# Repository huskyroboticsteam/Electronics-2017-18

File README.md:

# Electronics-2017-18

This is the 2017-18 Husky Robotics repository for electronics board designs and everything else electronics!

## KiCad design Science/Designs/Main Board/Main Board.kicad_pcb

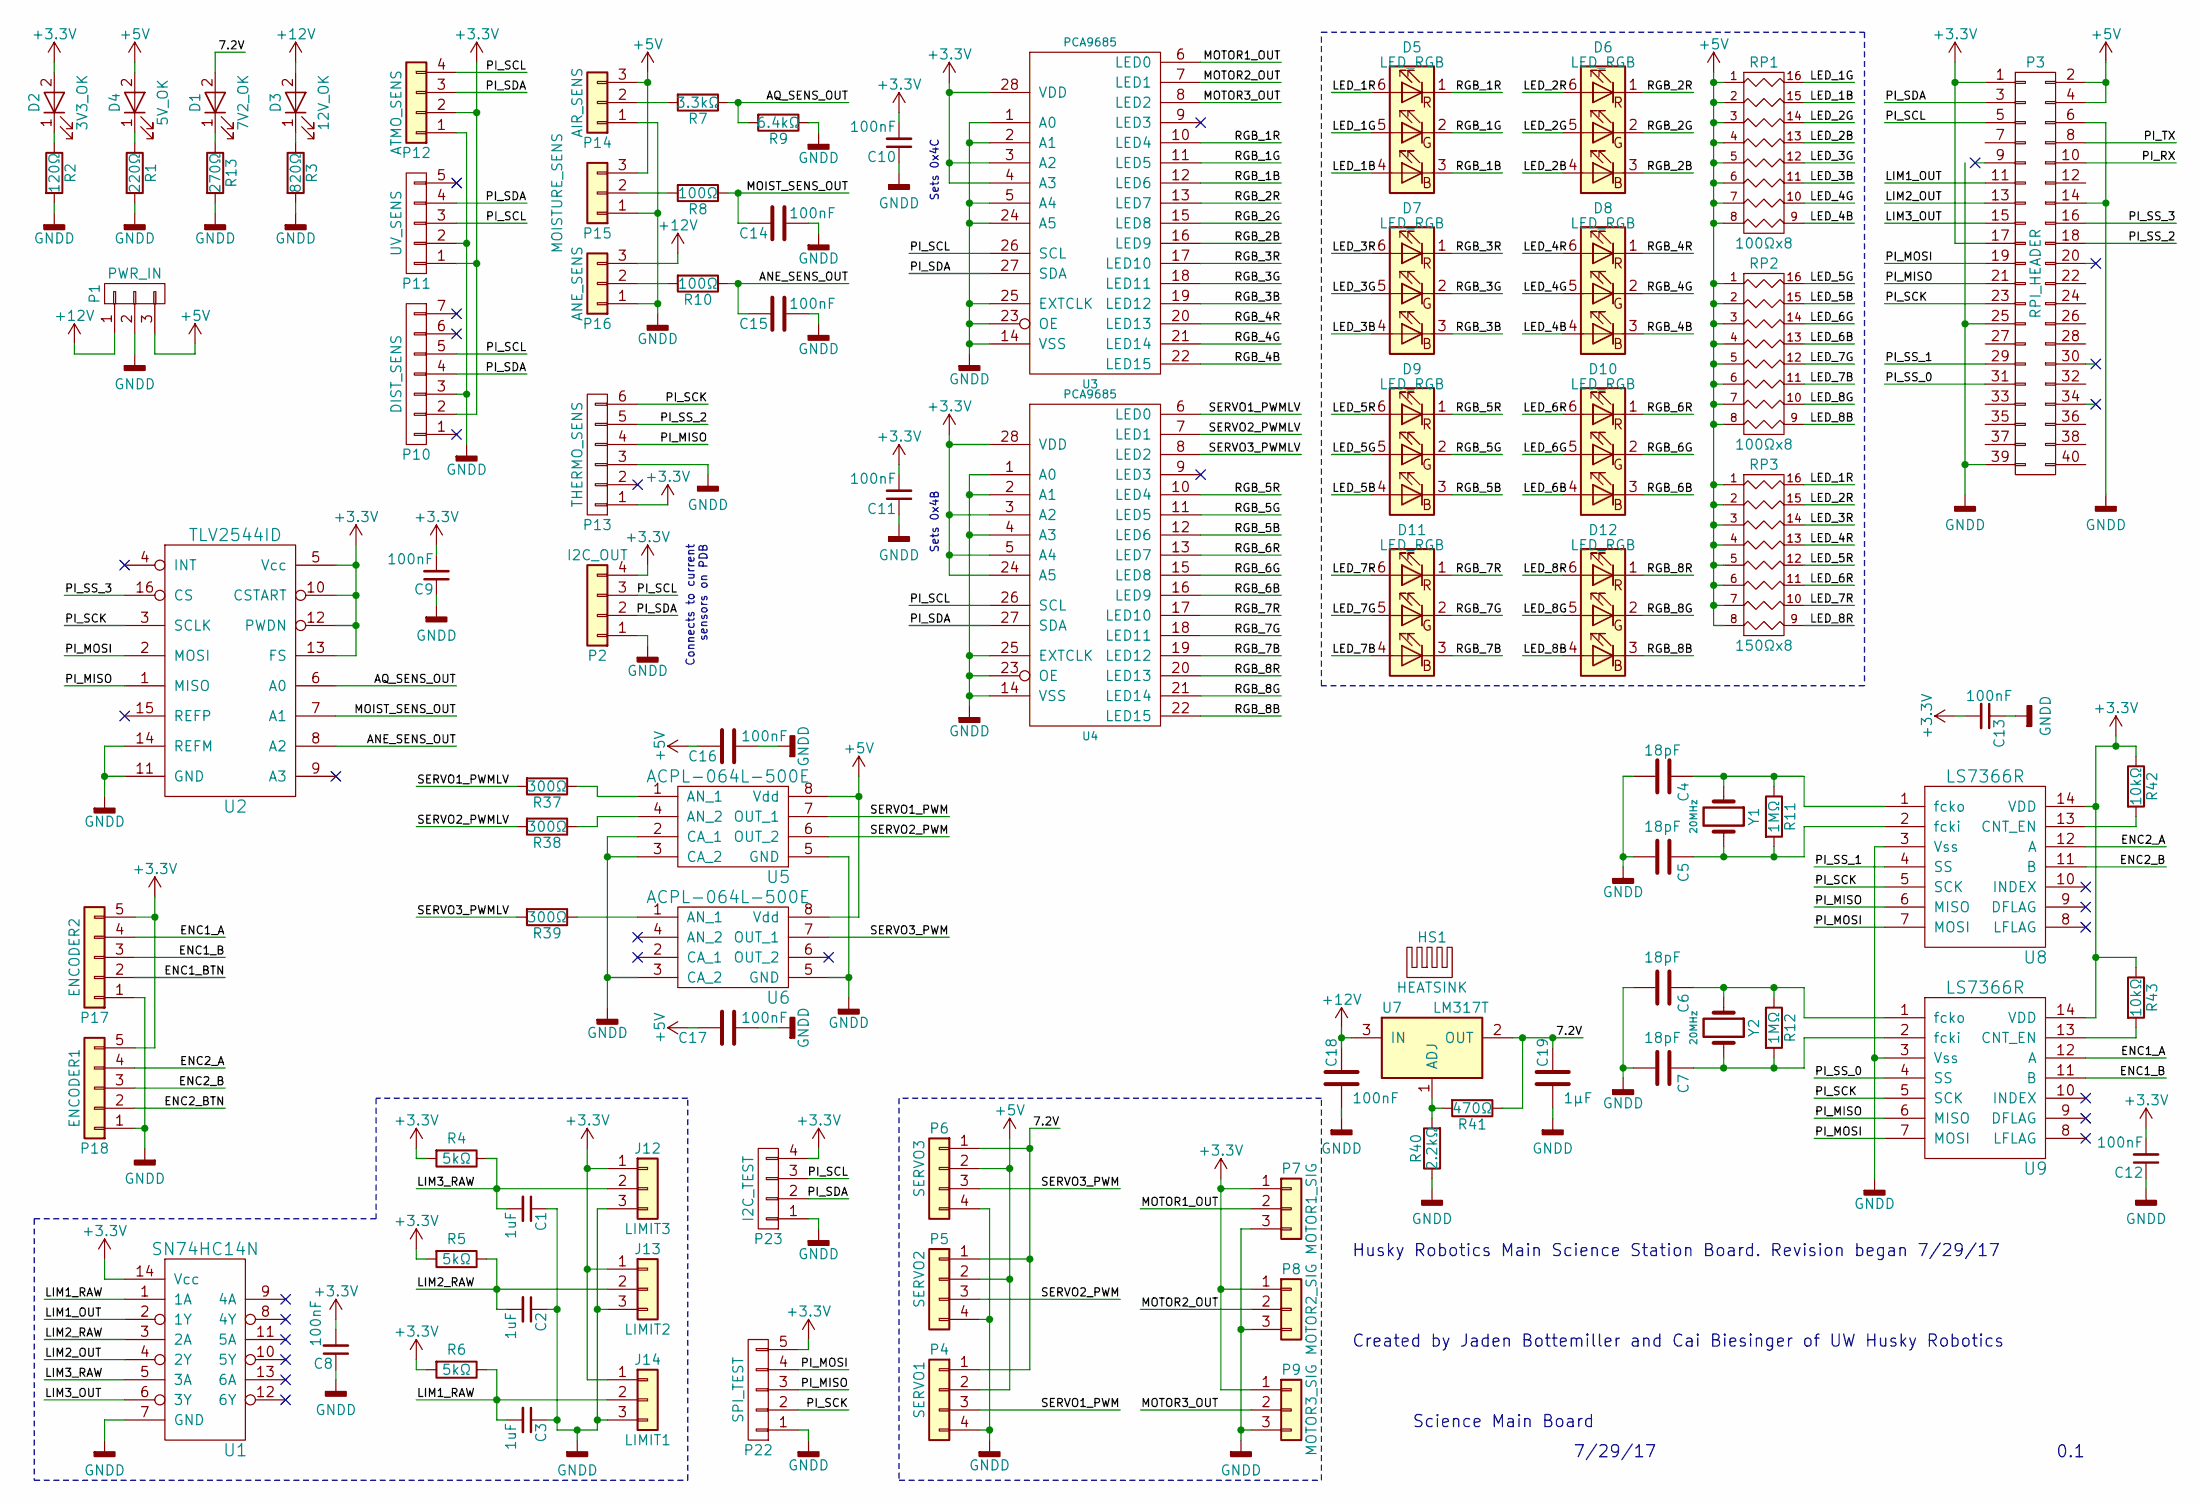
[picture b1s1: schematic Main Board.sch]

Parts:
C1, C2, C3: 1uF; C_1206_HandSoldering
C4, C5, C6, C7: 18pF; C_1206_HandSoldering
C8, C9, C10, C11, C12, C13, C14, C15, C16, C17, C18: 100nF; C_1206_HandSoldering
C19: 1µF; C_1206_HandSoldering
D1: 7V2_OK; LED_D5.0mm
D2: 3V3_OK; LED_D5.0mm
D3: 12V_OK; LED_D5.0mm
D4: 5V_OK; LED_D5.0mm
D5, D6, D7, D8, D9, D10, D11, D12: LED_RGB; SLV6A-FKB
HS1: HEATSINK; AAVID_531202B02500G
J12: LIMIT3; MOLEX_22-23-2031
J13: LIMIT2; MOLEX_22-23-2031
J14: LIMIT1; MOLEX_22-23-2031
P1: PWR_IN; PHOENIX_1792232
P2: I2C_OUT; MOLEX_22-23-2041
P3: RPI_HEADER; RPi-3B
P4: SERVO1; MOLEX_22-23-2041
P5: SERVO2; MOLEX_22-23-2041
P6: SERVO3; MOLEX_22-23-2041
P7: MOTOR1_SIG; MOLEX_22-23-2031
P8: MOTOR2_SIG; MOLEX_22-23-2031
P9: MOTOR3_SIG; MOLEX_22-23-2031
P10: DIST_SENS; MOLEX_22-23-2071
P11: UV_SENS; MOLEX_22-23-2051
P12: ATMO_SENS; MOLEX_22-23-2041
P13: THERMO_SENS; MOLEX_22-23-2061
P14: AIR_SENS; MOLEX_22-23-2031
P15: MOISTURE_SENS; MOLEX_22-23-2031
P16: ANE_SENS; MOLEX_22-23-2031
P17: ENCODER2; MOLEX_22-23-2051
P18: ENCODER1; MOLEX_22-23-2051
P22: SPI_TEST; Pin_Header_Straight_1x05_Pitch2.54mm
P23: I2C_TEST; Pin_Header_Straight_1x04_Pitch2.54mm
R1: 220Ω; R_1206_HandSoldering
R2: 120Ω; R_1206_HandSoldering
R3: 820Ω; R_1206_HandSoldering
R4, R5, R6: 5kΩ; R_1206_HandSoldering
R7: 3.3kΩ; R_1206_HandSoldering
R8, R10: 100Ω; R_1206_HandSoldering
R9: 6.4kΩ; R_1206_HandSoldering
R11, R12: 1MΩ; R_1206_HandSoldering
R13: 270Ω; R_1206_HandSoldering
R37, R38, R39: 300Ω; R_1206_HandSoldering
R40: 2.2kΩ; R_1206_HandSoldering
R41: 470Ω; R_1206_HandSoldering
R42, R43: 10kΩ; R_1206_HandSoldering
RP1, RP2: 100Ωx8; SOIC-16_3.9x9.9mm_Pitch1.27mm
RP3: 150Ωx8; SOIC-16_3.9x9.9mm_Pitch1.27mm
U1: SN74HC14N; SOIC-14_3.9x8.7mm_Pitch1.27mm
U2: TLV2544ID; SOIC-16_3.9x9.9mm_Pitch1.27mm
U3, U4: PCA9685; TSSOP-28_4.4x9.7mm_Pitch0.65mm
U5, U6: ACPL-064L-500E; SOIC-8_3.9x4.9mm_Pitch1.27mm
U7: LM317T; TO-220-3_Vertical
U8, U9: LS7366R; SOIC-14_3.9x8.7mm_Pitch1.27mm
Y1, Y2: 20MHz; HC-49USX

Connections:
+3V3: C8.2, C9.2, C10.2, C11.2, C12.2, C13.2, D2.2 (A), J12.1, J13.1, J14.1, P2.4, P3.1, P3.17, P7.1, P8.1, P9.1, P10.2, P11.1, P12.2, P13.1, P17.5, P18.5, P22.5, P23.4, R4.2, R5.2, R6.2, R42.1, R43.1, U1.14 (Vcc), U2.5 (Vcc), U2.10 (CSTART), U2.12 (PWDN), U2.13 (FS), U3.3 (A2), U3.4 (A3), U3.28 (VDD), U4.3 (A2), U4.5 (A4), U4.24 (A5), U4.28 (VDD), U8.14 (VDD), U9.14 (VDD)
+5V: C16.1, C17.1, D4.2 (A), P1.3, P3.2, P3.4, P4.2, P5.2, P6.2, P14.3, P15.3, RP1.1, RP1.2, RP1.3, RP1.4, RP1.5, RP1.6, RP1.7, RP1.8, RP2.1, RP2.2, RP2.3, RP2.4, RP2.5, RP2.6, RP2.7, RP2.8, RP3.1, RP3.2, RP3.3, RP3.4, RP3.5, RP3.6, RP3.7, RP3.8, U5.8 (Vdd), U6.8 (Vdd)
+12V: C18.1, D3.2 (A), P1.1, P16.3, U7.3 (IN)
/7.2V: C19.1, D1.2 (A), P4.1, P5.1, P6.1, R41.1, U7.2 (OUT)
/ANE_SENS_OUT: C15.2, R10.1, U2.8 (A2)
/AQ_SENS_OUT: R7.1, R9.2, U2.6 (A0)
/ENC1_A: P17.4, U9.12 (A)
/ENC1_B: P17.3, U9.11 (B)
/ENC1_BTN: P17.2
/ENC2_A: P18.4, U8.12 (A)
/ENC2_B: P18.3, U8.11 (B)
/ENC2_BTN: P18.2
/LED_1B: D5.4 (BA), RP1.15 (R2)
/LED_1G: D5.5 (GA), RP1.16 (R1)
/LED_1R: D5.6 (RA), RP3.16 (R1)
/LED_2B: D6.4 (BA), RP1.13 (R4)
/LED_2G: D6.5 (GA), RP1.14 (R3)
/LED_2R: D6.6 (RA), RP3.15 (R2)
/LED_3B: D7.4 (BA), RP1.11 (R6)
/LED_3G: D7.5 (GA), RP1.12 (R5)
/LED_3R: D7.6 (RA), RP3.14 (R3)
/LED_4B: D8.4 (BA), RP1.9 (R8)
/LED_4G: D8.5 (GA), RP1.10 (R7)
/LED_4R: D8.6 (RA), RP3.13 (R4)
/LED_5B: D9.4 (BA), RP2.15 (R2)
/LED_5G: D9.5 (GA), RP2.16 (R1)
/LED_5R: D9.6 (RA), RP3.12 (R5)
/LED_6B: D10.4 (BA), RP2.13 (R4)
/LED_6G: D10.5 (GA), RP2.14 (R3)
/LED_6R: D10.6 (RA), RP3.11 (R6)
/LED_7B: D11.4 (BA), RP2.11 (R6)
/LED_7G: D11.5 (GA), RP2.12 (R5)
/LED_7R: D11.6 (RA), RP3.10 (R7)
/LED_8B: D12.4 (BA), RP2.9 (R8)
/LED_8G: D12.5 (GA), RP2.10 (R7)
/LED_8R: D12.6 (RA), RP3.9 (R8)
/LIM1_OUT: P3.11, U1.2 (1Y)
/LIM1_RAW: C3.2, J14.2, R6.1, U1.1 (1A)
/LIM2_OUT: P3.13, U1.4 (2Y)
/LIM2_RAW: C2.2, J13.2, R5.1, U1.3 (2A)
/LIM3_OUT: P3.15, U1.6 (3Y)
/LIM3_RAW: C1.2, J12.2, R4.1, U1.5 (3A)
/MOIST_SENS_OUT: C14.2, R8.1, U2.7 (A1)
/MOTOR1_OUT: P7.2, U3.6 (LED0)
/MOTOR2_OUT: P8.2, U3.7 (LED1)
/MOTOR3_OUT: P9.2, U3.8 (LED2)
/PI_MISO: P3.21, P13.4, P22.3, U2.1 (MISO), U8.6 (MISO), U9.6 (MISO)
/PI_MOSI: P3.19, P22.4, U2.2 (MOSI), U8.7 (MOSI), U9.7 (MOSI)
/PI_RX: P3.10
/PI_SCK: P3.23, P13.6, P22.2, U2.3 (SCLK), U8.5 (SCK), U9.5 (SCK)
/PI_SCL: P2.3, P3.5, P10.5, P11.3, P12.4, P23.3, U3.26 (SCL), U4.26 (SCL)
/PI_SDA: P2.2, P3.3, P10.4, P11.4, P12.3, P23.2, U3.27 (SDA), U4.27 (SDA)
/PI_SS_0: P3.31, U9.4 (SS)
/PI_SS_1: P3.29, U8.4 (SS)
/PI_SS_2: P3.18, P13.5
/PI_SS_3: P3.16, U2.16 (CS)
/PI_TX: P3.8
/RGB_1B: D5.3 (BK), U3.12 (LED6)
/RGB_1G: D5.2 (GK), U3.11 (LED5)
/RGB_1R: D5.1 (RK), U3.10 (LED4)
/RGB_2B: D6.3 (BK), U3.16 (LED9)
/RGB_2G: D6.2 (GK), U3.15 (LED8)
/RGB_2R: D6.1 (RK), U3.13 (LED7)
/RGB_3B: D7.3 (BK), U3.19 (LED12)
/RGB_3G: D7.2 (GK), U3.18 (LED11)
/RGB_3R: D7.1 (RK), U3.17 (LED10)
/RGB_4B: D8.3 (BK), U3.22 (LED15)
/RGB_4G: D8.2 (GK), U3.21 (LED14)
/RGB_4R: D8.1 (RK), U3.20 (LED13)
/RGB_5B: D9.3 (BK), U4.12 (LED6)
/RGB_5G: D9.2 (GK), U4.11 (LED5)
/RGB_5R: D9.1 (RK), U4.10 (LED4)
/RGB_6B: D10.3 (BK), U4.16 (LED9)
/RGB_6G: D10.2 (GK), U4.15 (LED8)
/RGB_6R: D10.1 (RK), U4.13 (LED7)
/RGB_7B: D11.3 (BK), U4.19 (LED12)
/RGB_7G: D11.2 (GK), U4.18 (LED11)
/RGB_7R: D11.1 (RK), U4.17 (LED10)
/RGB_8B: D12.3 (BK), U4.22 (LED15)
/RGB_8G: D12.2 (GK), U4.21 (LED14)
/RGB_8R: D12.1 (RK), U4.20 (LED13)
/SERVO1_PWM: P4.3, U5.7 (OUT_1)
/SERVO1_PWMLV: R37.2, U4.6 (LED0)
/SERVO2_PWM: P5.3, U5.6 (OUT_2)
/SERVO2_PWMLV: R38.2, U4.7 (LED1)
/SERVO3_PWM: P6.3, U6.7 (OUT_1)
/SERVO3_PWMLV: R39.2, U4.8 (LED2)
GNDD: C1.1, C2.1, C3.1, C4.2, C5.2, C6.2, C7.2, C8.1, C9.1, C10.1, C11.1, C12.1, C13.1, C14.1, C15.1, C16.2, C17.2, C18.2, C19.2, J12.3, J13.3, J14.3, P1.2, P2.1, P3.6, P3.14, P3.25, P3.39, P4.4, P5.4, P6.4, P7.3, P8.3, P9.3, P10.3, P11.2, P12.1, P13.3, P14.1, P15.1, P16.1, P17.1, P18.1, P22.1, P23.1, R1.2, R2.2, R3.2, R9.1, R13.2, R40.1, U1.7 (GND), U2.11 (GND), U2.14 (REFM), U3.1 (A0), U3.2 (A1), U3.5 (A4), U3.14 (VSS), U3.23 (OE), U3.24 (A5), U3.25 (EXTCLK), U4.1 (A0), U4.2 (A1), U4.4 (A3), U4.14 (VSS), U4.23 (OE), U4.25 (EXTCLK), U5.2 (CA_1), U5.3 (CA_2), U5.5 (GND), U6.3 (CA_2), U6.5 (GND), U8.3 (Vss), U9.3 (Vss)
unnamed: C4.1, R11.1, U8.1 (fcko), Y1.1
unnamed: C5.1, R11.2, U8.2 (fcki), Y1.2
unnamed: C6.1, R12.1, U9.1 (fcko), Y2.1
unnamed: C7.1, R12.2, U9.2 (fcki), Y2.2
unnamed: D1.1 (K), R13.1
unnamed: D2.1 (K), R2.1
unnamed: D3.1 (K), R3.1
unnamed: D4.1 (K), R1.1
unnamed: P14.2, R7.2
unnamed: P15.2, R8.2
unnamed: P16.2, R10.2
unnamed: R37.1, U5.1 (AN_1)
unnamed: R38.1, U5.4 (AN_2)
unnamed: R39.1, U6.1 (AN_1)
unnamed: R40.2, R41.2, U7.1 (ADJ)
unnamed: R42.2, U8.13 (CNT_EN)
unnamed: R43.2, U9.13 (CNT_EN)

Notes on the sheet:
Husky Robotics Main Science Station Board. Revision began 7/29/17
Science Main Board
0.1
7/29/17
Created by Jaden Bottemiller and Cai Biesinger of UW Husky Robotics
Sets 0x4B
Sets 0x4C
Connects to current sensors on PDB

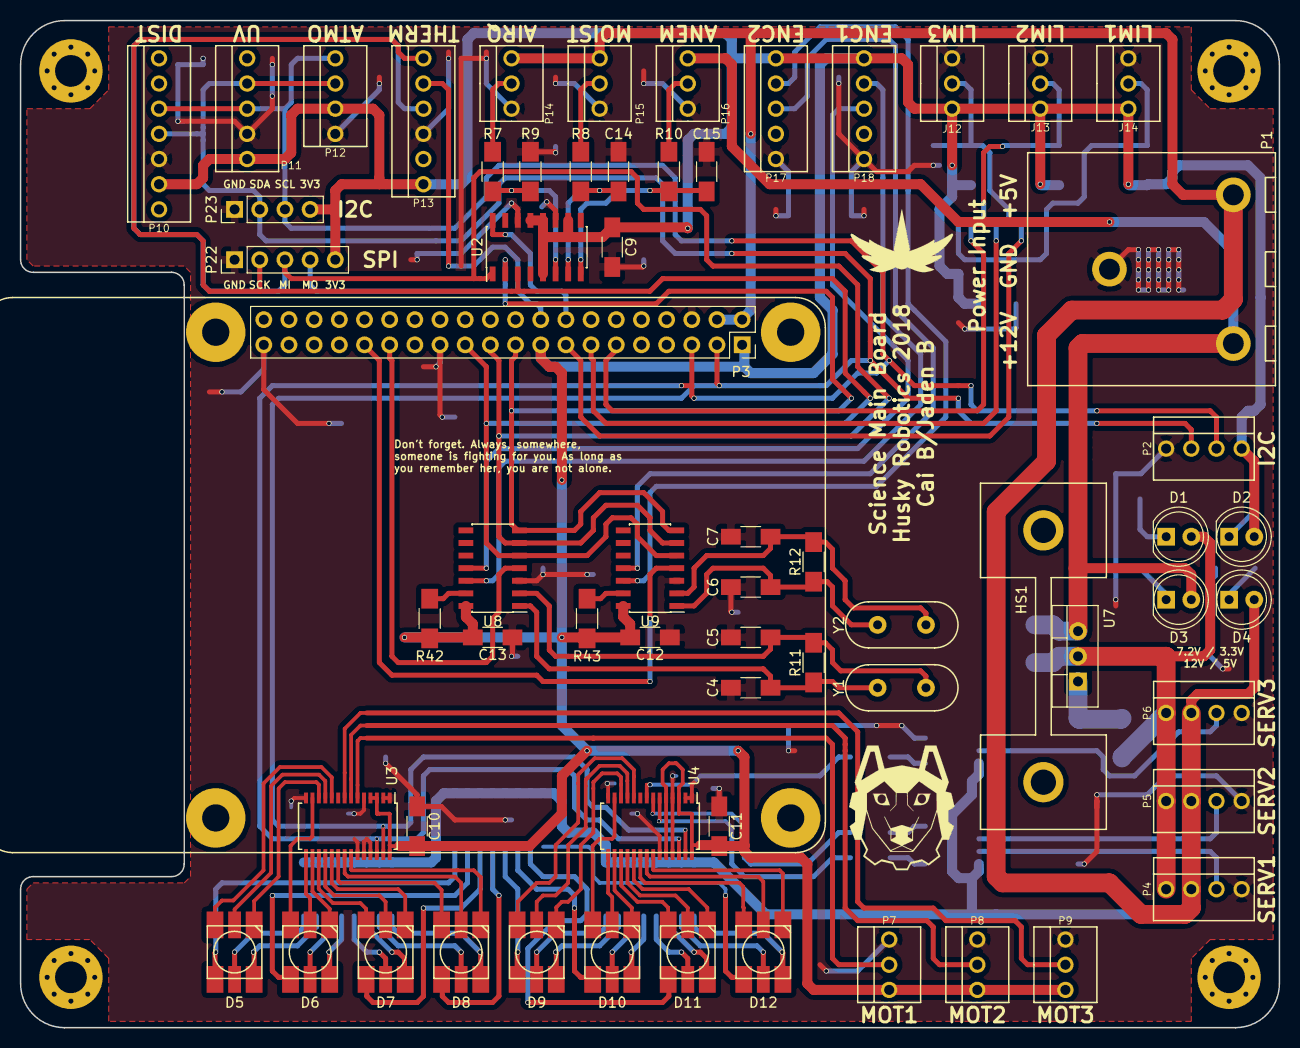
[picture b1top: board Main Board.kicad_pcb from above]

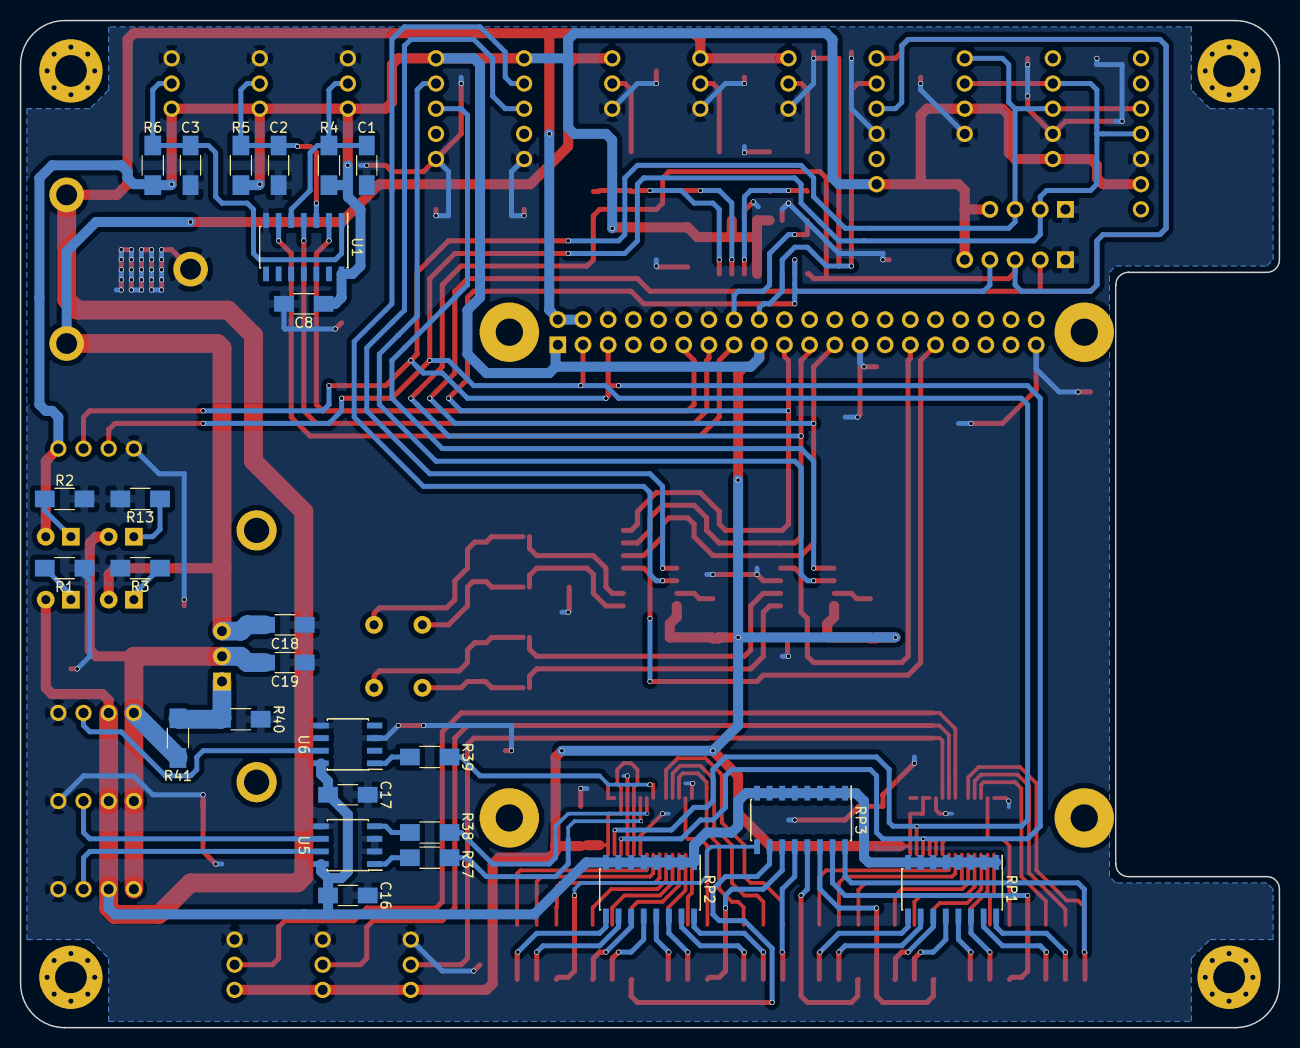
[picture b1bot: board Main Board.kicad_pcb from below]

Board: 2 copper layers, 127.0 x 101.6 mm, 89 parts (26 on the bottom side), 101 nets.

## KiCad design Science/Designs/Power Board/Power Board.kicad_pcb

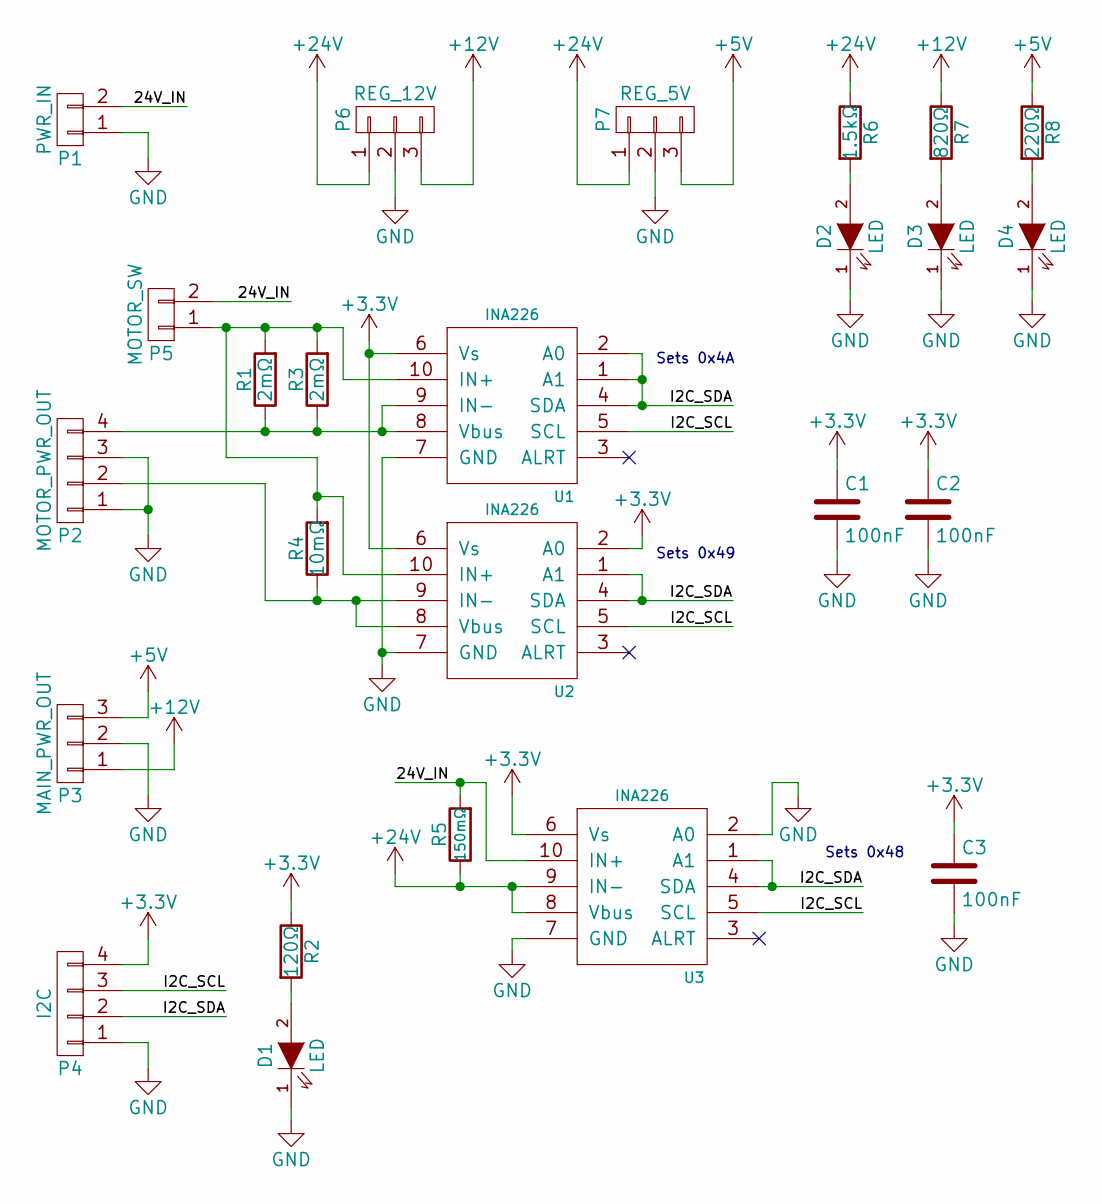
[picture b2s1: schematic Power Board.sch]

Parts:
C1, C2, C3: 100nF; C_1206_HandSoldering
D1, D2, D3, D4: LED; LED_D5.0mm
P1: PWR_IN; PHOENIX_1792229
P2: MOTOR_PWR_OUT; PHOENIX_1792245
P3: MAIN_PWR_OUT; PHOENIX_1792232
P4: I2C; MOLEX_22-23-2041
P5: MOTOR_SW; PHOENIX_1792229
P6: REG_12V; PHOENIX_1792232
P7: REG_5V; PHOENIX_1792232
R1, R3: 2mΩ; 2526W
R2: 120Ω; R_1206_HandSoldering
R4: 10mΩ; 2827W
R5: 150mΩ; R_Axial_Power_L25.0mm_W6.4mm_P30.48mm
R6: 1.5kΩ; R_1206_HandSoldering
R7: 820Ω; R_1206_HandSoldering
R8: 220Ω; R_1206_HandSoldering
U1, U2, U3: INA226; MSOP-10_3x3mm_Pitch0.5mm

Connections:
+3V3: C1.1, C2.1, C3.1, P4.4, R2.1, U1.6 (Vs), U2.2 (A0), U2.6 (Vs), U3.6 (Vs)
+5V: P3.3, P7.3, R8.1
+12V: P3.1, P6.3, R7.1
+24V: P6.1, P7.1, R5.1, R6.1, U3.8 (Vbus), U3.9 (IN-)
/24V_IN: P1.2, P5.2, R5.2, U3.10 (IN+)
/I2C_SCL: P4.3, U1.5 (SCL), U2.5 (SCL), U3.5 (SCL)
/I2C_SDA: P4.2, U1.1 (A1), U1.2 (A0), U1.4 (SDA), U2.1 (A1), U2.4 (SDA), U3.1 (A1), U3.4 (SDA)
GND: C1.2, C2.2, C3.2, D1.1 (K), D2.1 (K), D3.1 (K), D4.1 (K), P1.1, P2.1, P2.3, P3.2, P4.1, P6.2, P7.2, U1.7 (GND), U2.7 (GND), U3.2 (A0), U3.7 (GND)
unnamed: D1.2 (A), R2.2
unnamed: D2.2 (A), R6.2
unnamed: D3.2 (A), R7.2
unnamed: D4.2 (A), R8.2
unnamed: P2.2, R4.1, U2.8 (Vbus), U2.9 (IN-)
unnamed: P2.4, R1.1, R3.1, U1.8 (Vbus), U1.9 (IN-)
unnamed: P5.1, R1.2, R3.2, R4.2, U1.10 (IN+), U2.10 (IN+)

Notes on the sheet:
Sets 0x4A
Sets 0x49
Sets 0x48

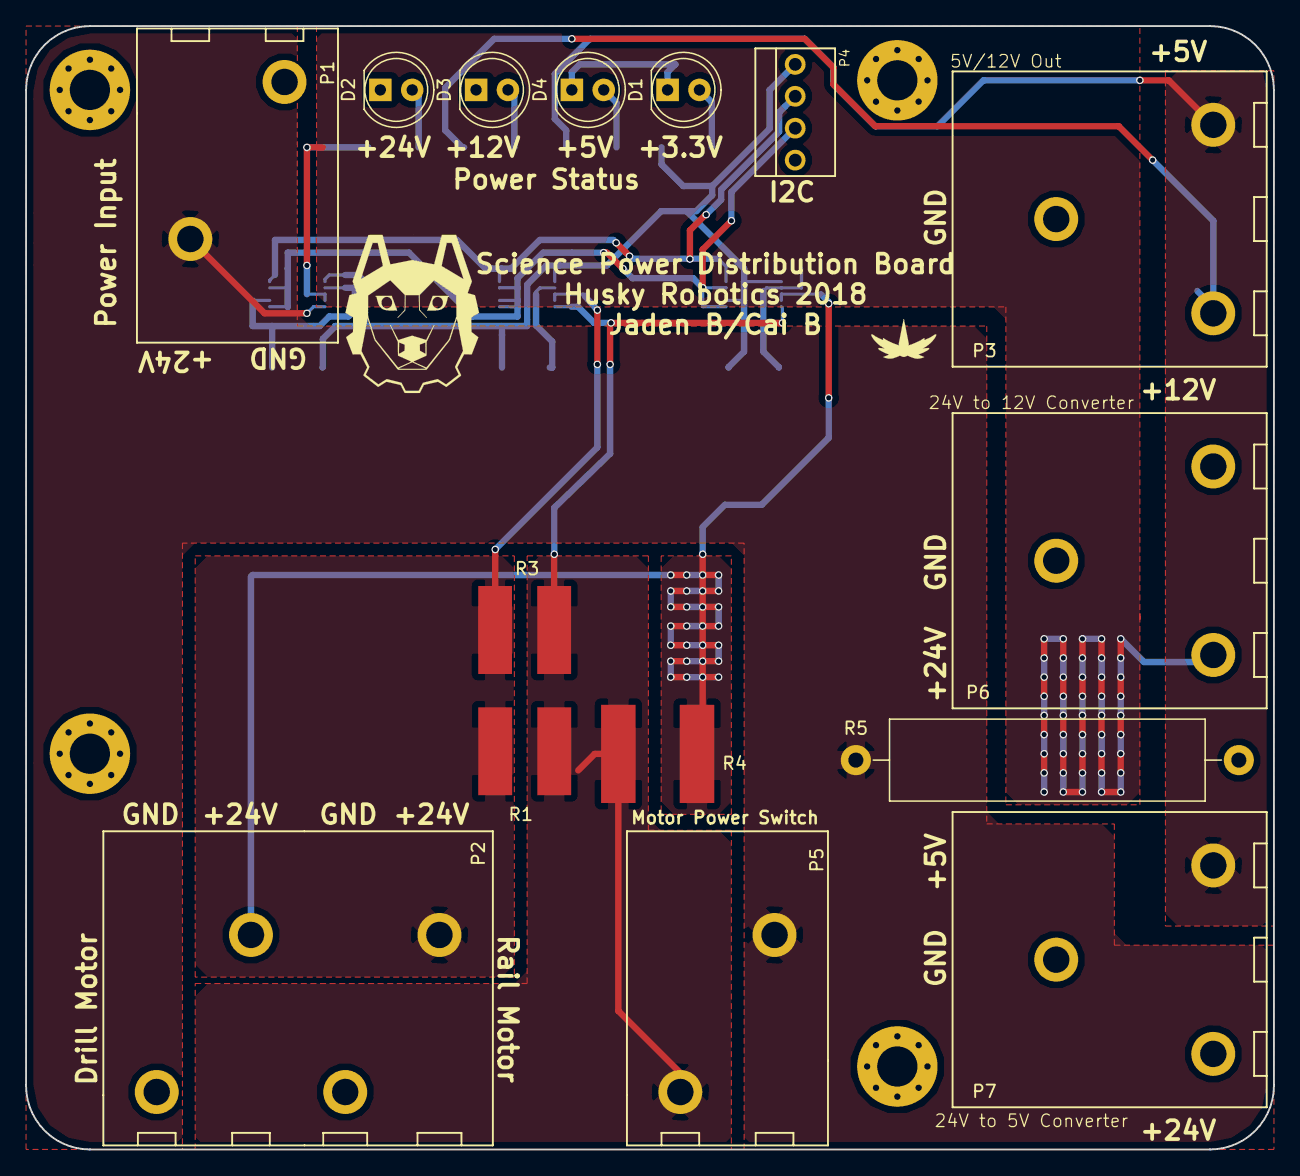
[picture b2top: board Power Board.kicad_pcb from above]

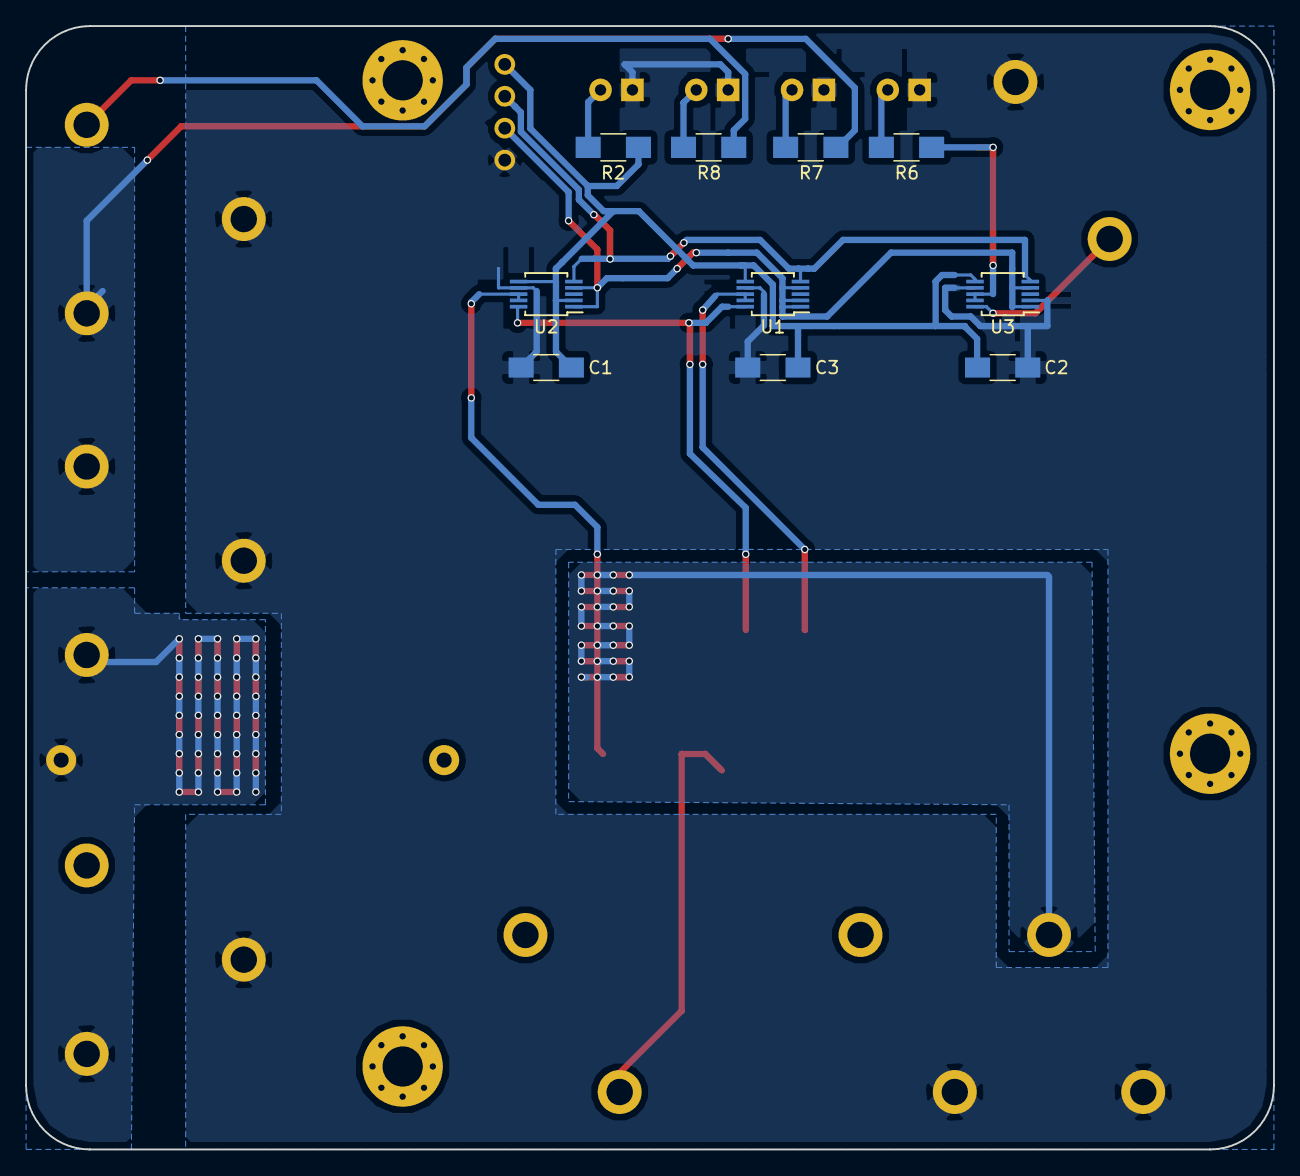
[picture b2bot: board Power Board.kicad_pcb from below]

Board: 2 copper layers, 99.3 x 89.4 mm, 25 parts (10 on the bottom side), 15 nets.

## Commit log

2017-12-02 Added empty readme
2017-12-02 Added existing Science designs.
2017-12-02 added Eagle folder
2017-12-02 Added Servo outputs
    Removed Encoder debouncing
2017-12-02 Actually saved this time
2017-12-02 Merged KiCad Libraries
    Now we have one "sciencelib" instead of 3. Releavnt changes made in schematics.
2017-12-02 Changed labelling standard for main board
2017-12-02 Current sensing on power board
2017-12-03 added eagle lbrs
2017-12-05 Added power pinouts and servo connections
2017-12-08 eagle lbr updates
2017-12-09 Changed LS7366R implementation per spec
2017-12-10 eagle gps
2017-12-23 chassis PDB in layout
2017-12-23 PDB mid dev
2017-12-23 pdb rev a
2018-01-07 Added sensor connections
2018-01-07 Added TLV2544ID to library
2018-01-07 Added ADC to main board schematic
2018-01-07 Updated schematic with new ADC layout
2018-01-07 Aded PWM device to schematic
2018-01-10 Adding component values, system current sensor
2018-01-12 Added decoupling capacitors, started component associatons, added RGB LEDs
2018-01-12 Cleaning up schematic, adding I2C test connector
2018-01-13 Fixing various board issues
    Decoupling caps, power connector, sensor connectors, power LEDs, etc.
2018-01-13 Added IC datasheets
2018-01-13 Added cable connector datasheets
2018-01-13 Fixed issues
2018-01-13 Added missing pullup
2018-01-13 Added optocouplers to servo outputs
2018-01-13 Fixed optocoupler
2018-01-13 Added connectors
2018-01-13 Added 7.2V regulator
2018-01-13 Schematic cleanup
2018-01-13 Switched to resistor networks for RGB LEDs
2018-01-13 Began Main board layout
2018-01-13 Continued working on main PCB
2018-01-14 Added BAC connectors to library
2018-01-14 Added RPi and Crystal Footprints
2018-01-14 Fixed RPi Footprint
    Someone (me) got the outline flipped...
2018-01-14 Added RGB LED footprint, working on layout
2018-01-14 Working on PCB
2018-01-14 Continuing PCB some more
2018-01-14 Began Power Board layout
2018-01-14 Added heatsink footprint
2018-01-14 Continued continuing on main board
2018-01-14 Updated footprint library
2018-01-14 "Finished routing"
    Except not really because it sucks
2018-01-14 Final PDB changes for tonight
2018-01-14 Last schematic changes for the night
2018-01-14 Finishing up for tonight.
2018-01-14 Changed layout again
    Could definitely still use some work...
2018-01-14 Finished way better layout
2018-01-14 Removed uneccessary vias
2018-01-14 Edited silkscreen
2018-01-14 Added CAD files for 3-PIN molex connector
2018-01-15 Added 4-PIN MOLEX CAD
2018-01-15 More layout
2018-01-15 Updated footprints
2018-01-15 Even more layout
2018-01-15 Added mounting holes
2018-01-15 Done for the nigtht.
    Good progress!
2018-01-15 Layout nearing completion.
2018-01-17 Small track updates
2018-01-20 Continued work on main board layout. Nearing completion!
2018-01-20 Continuing layout work
2018-01-20 Almost done
2018-01-21 Very close to finished main board
    Just needs ground plane work now!
2018-01-21 Redesign started. Looks better, although still has issues
2018-01-21 Ground planes almost done
2018-01-21 All connections made
    I think I am within spec as much as I can be. Maybe we should go with 2oz copper on this board
2018-01-21 Fixed polygon combination
2018-01-21 Last trace changes
    Will work on solder mask now
2018-01-21 Stripped away soldermask on front and back
2018-01-21 Main Board finished?
2018-01-21 Fixing issues, adding logos
2018-01-22 Fixed polygons
2018-01-22 I think the Science PDB is done
2018-01-22 Added I2C label
    (Spoke too soon)
2018-01-22 Moved a few component designators
2018-01-22 updated eagle files
2018-01-22 squeezed
2018-01-22 Final changes
    (I didn't save apparently)
2018-01-22 Replaced current sensor with INA226
2018-01-22 Forgot to save schematic changes
2018-01-23 Added Labels
    PDB is officially done
2018-01-23 Last-minute changes and production output for main board
2018-01-23 PDB production output
2018-04-15 Fixing address error
2018-06-11 encoder counter brd in layout
2018-06-29 pre silk encoder brds. layout ready for review
2018-07-02 encoder boards done
2018-07-21 printed designs with gerbers
2018-10-05 Added new board (in prog)
2018-10-05 Added UART/USB, JTAG, I2C outputs for programming
2018-10-05 Changed components
2018-10-06 Spent more time on models than I would have like to
2018-10-06 Actually added the model to the part...
2018-10-06 Saving projects isn't completely intiuitive to me yet
2018-10-06 Continuing work
2018-10-08 Worked on power for a bit
